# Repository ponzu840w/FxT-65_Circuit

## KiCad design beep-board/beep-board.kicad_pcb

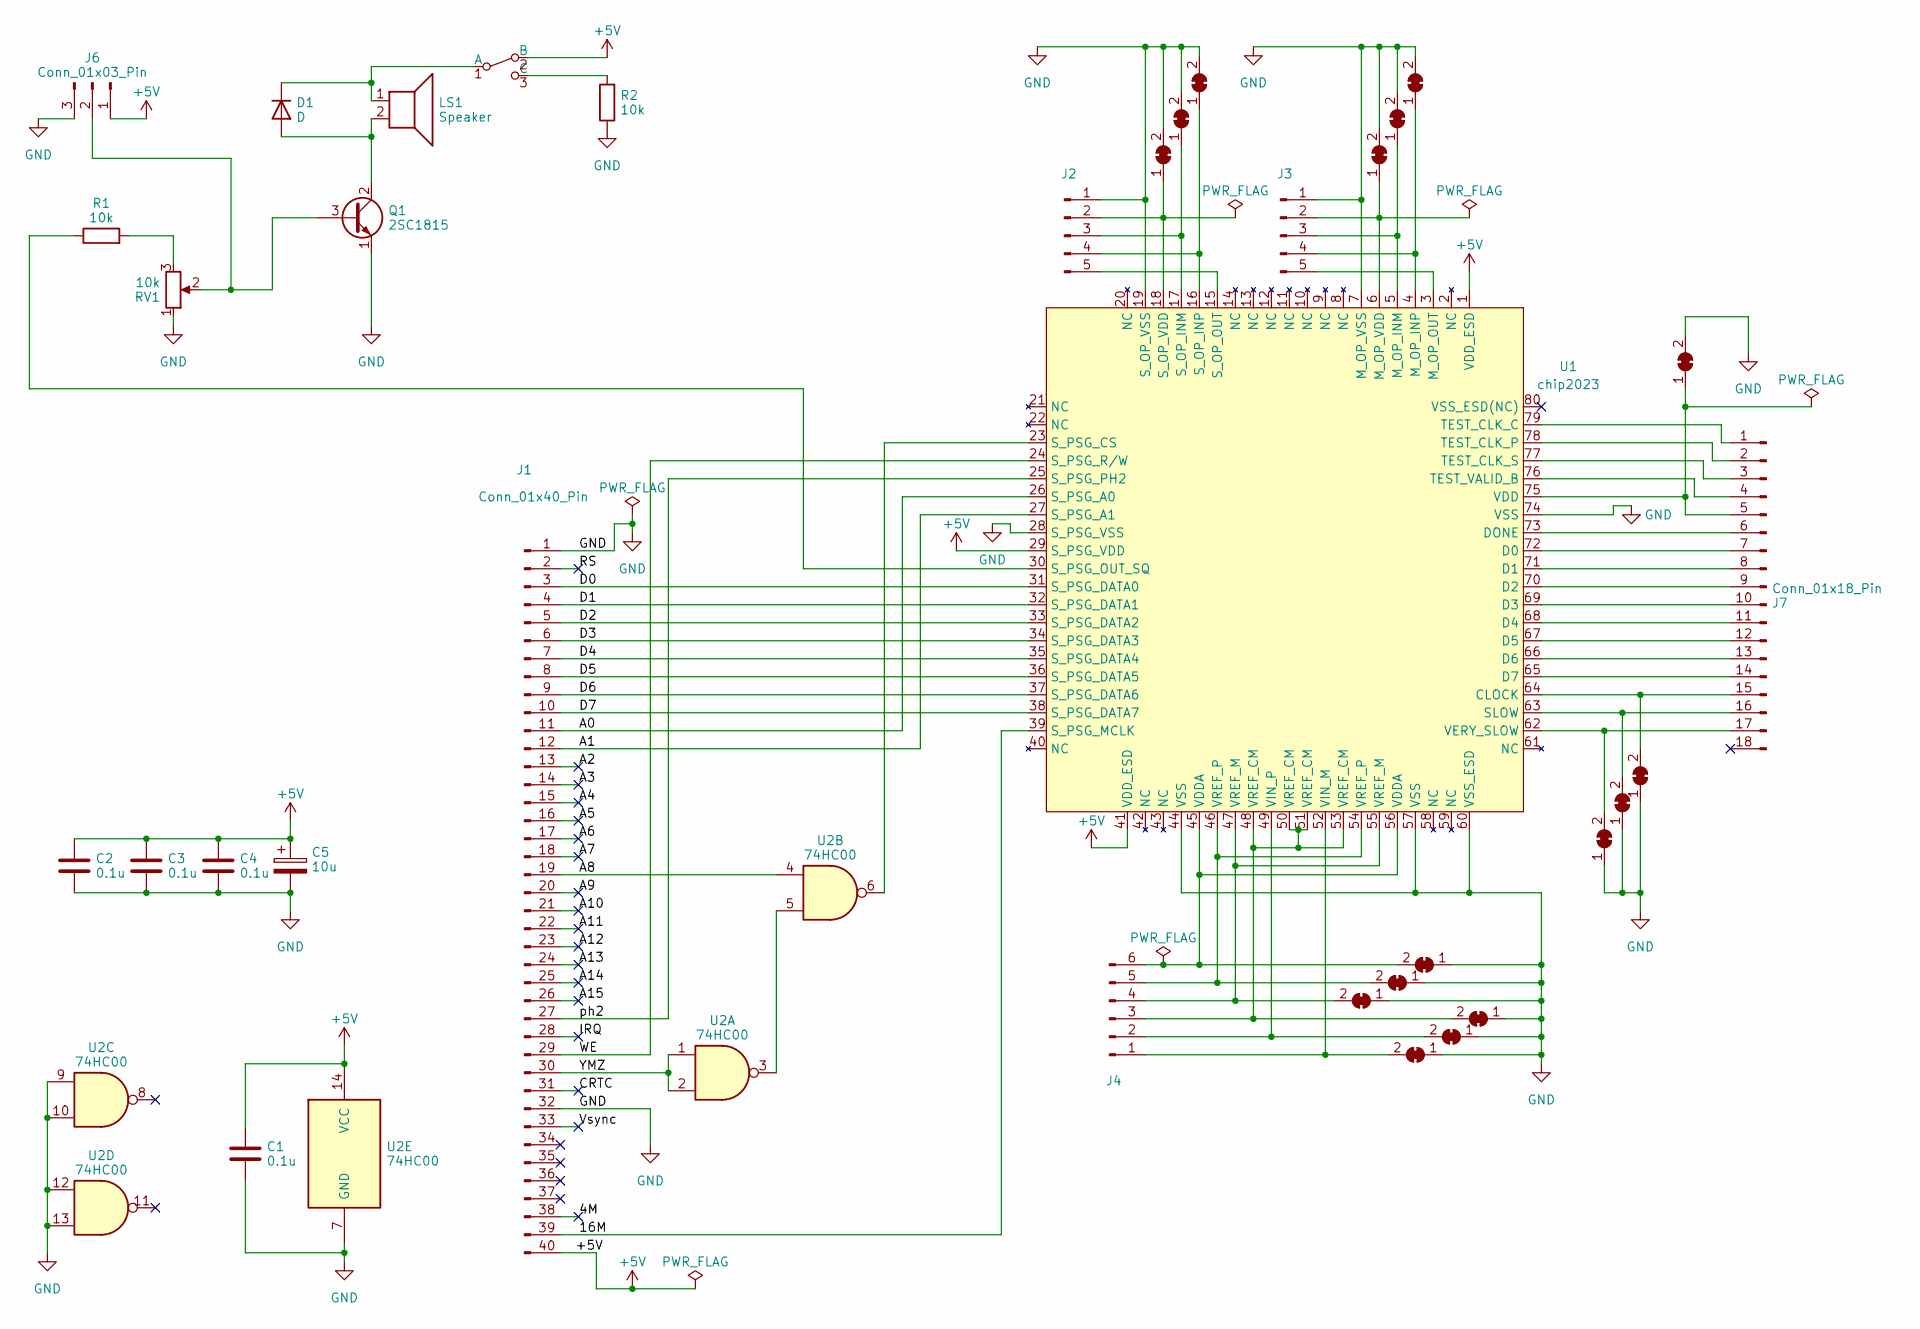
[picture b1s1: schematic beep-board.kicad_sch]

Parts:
C1, C2, C3, C4: 0.1u; C_0603_1608Metric_Pad1.08x0.95mm_HandSolder
C5: 10u; CP_Radial_D6.3mm_P2.50mm
D1: D; D_DO-34_SOD68_P7.62mm_Horizontal
J1: Conn_01x40_Pin; PinHeader_2x20_P2.54mm_Horizontal
J2, J3: Conn_01x05_Pin; PinHeader_1x05_P2.54mm_Horizontal
J4: Conn_01x06_Pin; PinHeader_1x06_P2.54mm_Horizontal
J6: Conn_01x03_Pin; PinSocket_1x03_P2.54mm_Horizontal
J7: Conn_01x18_Pin; PinHeader_2x09_P2.54mm_Horizontal
JP1, JP2, JP3, JP4, JP5, JP6, JP7, JP8, JP9, JP10, JP11, JP12, JP13, JP14, JP15, JP17: SolderJumper_2_Bridged; SolderJumper-2_P1.3mm_Bridged2Bar_RoundedPad1.0x1.5mm
LS1: Speaker; UGCT7525AN4
Q1: 2SC1815; TO-92
R1, R2: 10k; R_Axial_DIN0207_L6.3mm_D2.5mm_P7.62mm_Horizontal
RV1: 10k; RK10J12E0A0A
SW1: SW_SPDT; ISH-1260-HA-G
U1: chip2023; TQFP-80_12x12mm_P0.5mm
U2: 74HC00; DIP-14_W7.62mm_Socket_LongPads

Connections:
+5V: C1.1, C2.1, C3.1, C4.1, C5.1, J1.40, J6.1, SW1.2 (B), U1.1 (VDD_ESD), U1.29 (S_PSG_VDD), U1.41 (VDD_ESD), U2.14 (VCC)
/4M: J1.38
/16M: J1.39, U1.39 (S_PSG_MCLK)
/A0: J1.11, U1.26 (S_PSG_A0)
/A1: J1.12, U1.27 (S_PSG_A1)
/A2: J1.13
/A3: J1.14
/A4: J1.15
/A5: J1.16
/A6: J1.17
/A7: J1.18
/A8: J1.19, U2.4
/A9: J1.20
/A10: J1.21
/A11: J1.22
/A12: J1.23
/A13: J1.24
/A14: J1.25
/A15: J1.26
/CRTC: J1.31
/D0: J1.3, U1.31 (S_PSG_DATA0)
/D1: J1.4, U1.32 (S_PSG_DATA1)
/D2: J1.5, U1.33 (S_PSG_DATA2)
/D3: J1.6, U1.34 (S_PSG_DATA3)
/D4: J1.7, U1.35 (S_PSG_DATA4)
/D5: J1.8, U1.36 (S_PSG_DATA5)
/D6: J1.9, U1.37 (S_PSG_DATA6)
/D7: J1.10, U1.38 (S_PSG_DATA7)
/IRQ: J1.28
/RS: J1.2
/Vsync: J1.33
/WE: J1.29, U1.24 (S_PSG_R/W)
/YMZ: J1.30, U2.1, U2.2
/ph2: J1.27, U1.25 (S_PSG_PH2)
GND: C1.2, C2.2, C3.2, C4.2, C5.2, J1.1, J1.32, J2.1, J3.1, J6.3, JP1.2 (B), JP2.2 (B), JP3.2 (B), JP4.2 (B), JP5.2 (B), JP6.2 (B), JP7.1 (A), JP8.1 (A), JP9.1 (A), JP10.1 (A), JP11.1 (A), JP12.1 (A), JP13.1 (A), JP14.1 (A), JP15.1 (A), JP17.2 (B), Q1.1 (E), R2.1, RV1.1, U1.7 (M_OP_VSS), U1.19 (S_OP_VSS), U1.28 (S_PSG_VSS), U1.44 (VSS), U1.57 (VSS), U1.60 (VSS_ESD), U1.74 (VSS), U2.7 (GND), U2.9, U2.10, U2.12, U2.13
unnamed: D1.2 (A), LS1.2, Q1.2 (C)
unnamed: D1.1 (K), LS1.1, SW1.1 (A)
unnamed: J2.2, JP17.1 (A), U1.18 (S_OP_VDD)
unnamed: J2.3, JP1.1 (A), U1.17 (S_OP_INM)
unnamed: J2.4, JP2.1 (A), U1.16 (S_OP_INP)
unnamed: J2.5, U1.15 (S_OP_OUT)
unnamed: J3.2, JP3.1 (A), U1.6 (M_OP_VDD)
unnamed: J3.3, JP4.1 (A), U1.5 (M_OP_INM)
unnamed: J3.4, JP5.1 (A), U1.4 (M_OP_INP)
unnamed: J3.5, U1.3 (M_OP_OUT)
unnamed: J4.1, JP9.2 (B), U1.52 (VIN_M)
unnamed: J4.2, JP8.2 (B), U1.49 (VIN_P)
unnamed: J4.3, JP7.2 (B), U1.48 (VREF_CM), U1.50 (VREF_CM), U1.51 (VREF_CM), U1.53 (VREF_CM)
unnamed: J4.4, JP10.2 (B), U1.47 (VREF_M), U1.55 (VREF_M)
unnamed: J4.5, JP11.2 (B), U1.46 (VREF_P), U1.54 (VREF_P)
unnamed: J4.6, JP12.2 (B), U1.45 (VDDA), U1.56 (VDDA)
unnamed: J6.2, Q1.3 (B), RV1.2
unnamed: J7.1, U1.79 (TEST_CLK_C)
unnamed: J7.2, U1.78 (TEST_CLK_P)
unnamed: J7.3, U1.77 (TEST_CLK_S)
unnamed: J7.4, U1.76 (TEST_VALID_B)
unnamed: J7.5, JP6.1 (A), U1.75 (VDD)
unnamed: J7.6, U1.73 (DONE)
unnamed: J7.7, U1.72 (D0)
unnamed: J7.8, U1.71 (D1)
unnamed: J7.9, U1.70 (D2)
unnamed: J7.10, U1.69 (D3)
unnamed: J7.11, U1.68 (D4)
unnamed: J7.12, U1.67 (D5)
unnamed: J7.13, U1.66 (D6)
unnamed: J7.14, U1.65 (D7)
unnamed: J7.15, JP15.2 (B), U1.64 (CLOCK)
unnamed: J7.16, JP14.2 (B), U1.63 (SLOW)
unnamed: J7.17, JP13.2 (B), U1.62 (VERY_SLOW)
unnamed: R1.2, RV1.3
unnamed: R2.2, SW1.3 (C)
unnamed: U1.23 (S_PSG_CS), U2.6
unnamed: R1.1, U1.30 (S_PSG_OUT_SQ)
unnamed: U2.3, U2.5

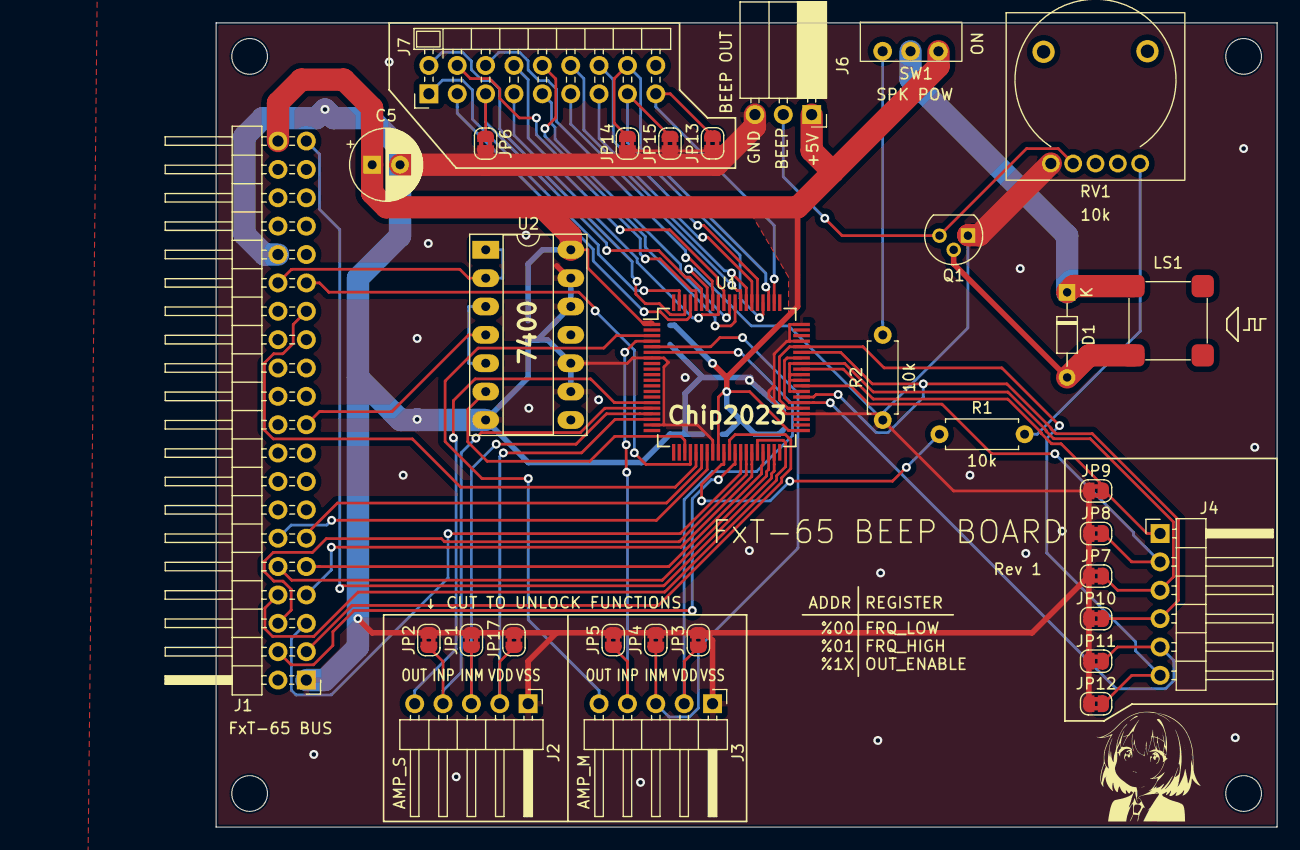
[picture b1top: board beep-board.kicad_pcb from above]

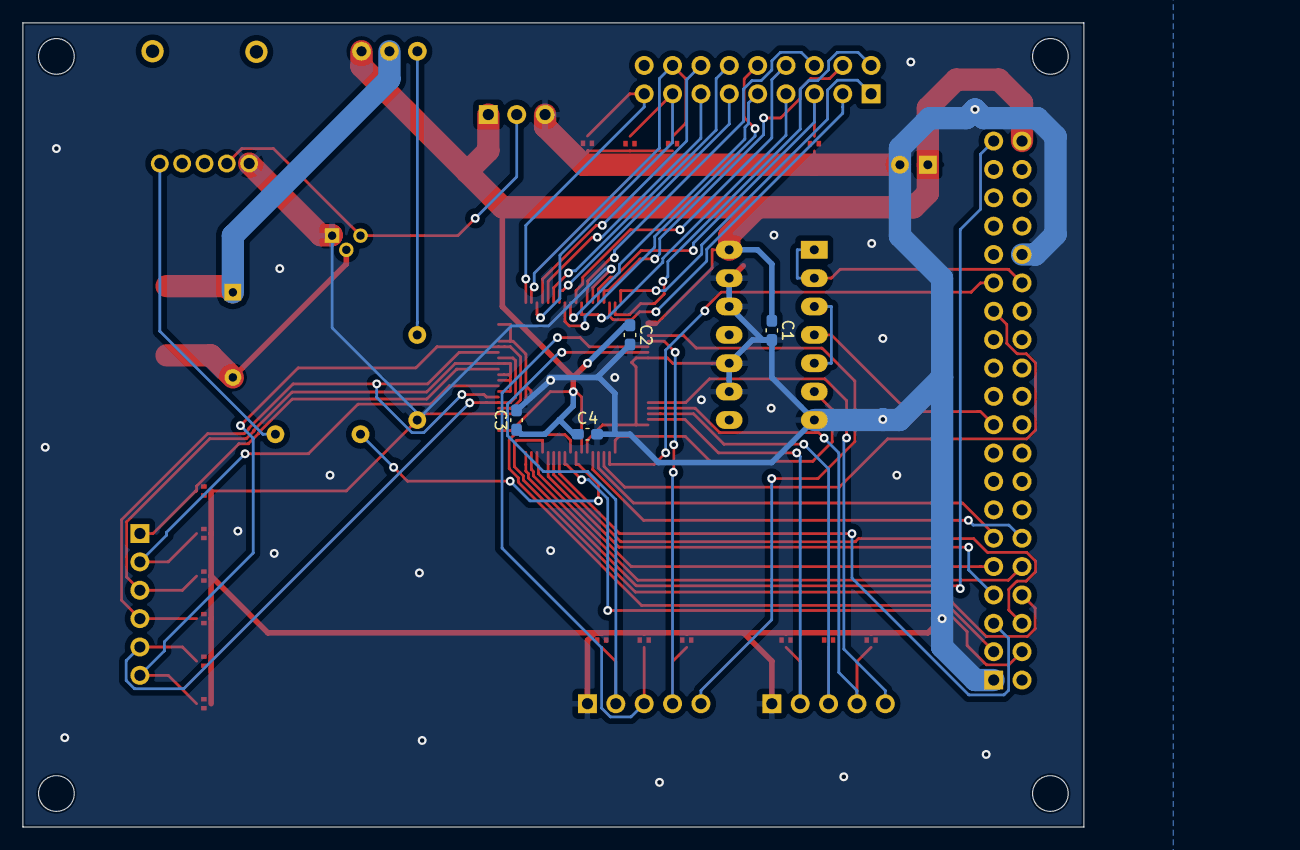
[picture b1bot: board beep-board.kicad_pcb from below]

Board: 2 copper layers, 112.3 x 72.0 mm, 36 parts (4 on the bottom side), 56 nets.

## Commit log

2025-10-20 init
2025-10-20 マザボ回路を追加
2025-10-20 全ボードを追加
